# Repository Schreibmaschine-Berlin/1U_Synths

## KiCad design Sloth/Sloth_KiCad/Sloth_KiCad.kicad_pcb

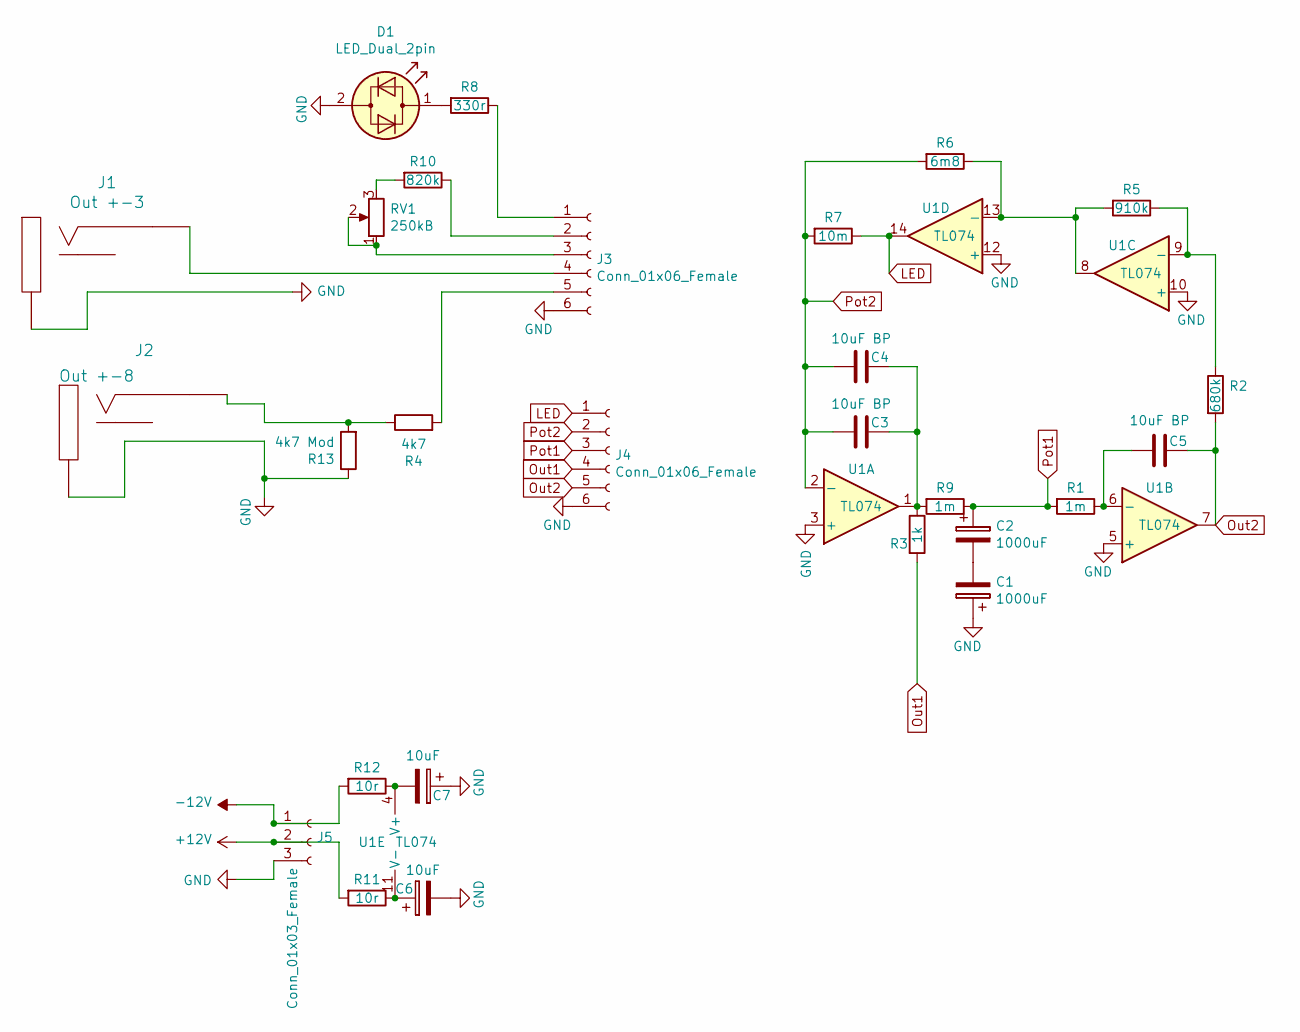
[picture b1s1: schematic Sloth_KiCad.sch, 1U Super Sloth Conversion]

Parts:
C1, C2: 1000uF; CP_Elec_10x10
C3, C4, C5: 10uF BP; CP_Elec_6.3x5.4_Nichicon
C6, C7: 10uF; CP_Elec_5x4.5
D1: LED_Dual_2pin; LED_D3.0mm
J1: Out +-3; PJ301M-12
J2: Out +-8; PJ301M-12
J3, J4: Conn_01x06_Female; PinHeader_1x06_P2.54mm_Vertical
J5: Conn_01x03_Female; PinHeader_1x03_P2.54mm_Vertical
R1, R9: 1m; R_0603_1608Metric_Pad1.05x0.95mm_HandSolder
R2: 680k; R_0603_1608Metric_Pad1.05x0.95mm_HandSolder
R3: 1k; R_0603_1608Metric_Pad1.05x0.95mm_HandSolder
R4: 4k7; R_0603_1608Metric_Pad1.05x0.95mm_HandSolder
R5: 910k; R_0603_1608Metric_Pad1.05x0.95mm_HandSolder
R6: 6m8; R_0603_1608Metric_Pad1.05x0.95mm_HandSolder
R7: 10m; R_0603_1608Metric_Pad1.05x0.95mm_HandSolder
R8: 330r; R_0603_1608Metric_Pad1.05x0.95mm_HandSolder
R10: 820k; R_0603_1608Metric_Pad1.05x0.95mm_HandSolder
R11, R12: 10r; R_0603_1608Metric_Pad1.05x0.95mm_HandSolder
R13: 4k7 Mod; R_0603_1608Metric_Pad1.05x0.95mm_HandSolder
RV1: 250kB; Potentiometer_Alps_RK09K_Single_Vertical
U1: TL074; SOIC-14_3.9x8.7mm_P1.27mm

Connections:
+12V: J5.2, R11.2
-12V: J5.1, R12.2
GND: C1.1, C6.2, C7.1, D1.2 (AK), J1.2 (SHEILD), J2.2 (SHEILD), J3.6, J4.6, J5.3, R13.1, U1.3 (+), U1.5 (+), U1.10 (+), U1.12 (+)
LED: J4.1, R7.1, U1.14
unnamed: C1.2, C2.2
unnamed: C3.1, C4.1, R3.1, R9.2, U1.1
unnamed: C5.2, R1.1, U1.6 (-)
unnamed: C6.1, R11.1, U1.11 (V-)
unnamed: C7.2, R12.1, U1.4 (V+)
unnamed: D1.1 (KA), R8.2
unnamed: J1.1 (SIG), J3.4
unnamed: J2.1 (SIG), R4.1, R13.2
unnamed: J3.1, R8.1
unnamed: J3.2, R10.1
unnamed: J3.3, RV1.1, RV1.2
unnamed: J3.5, R4.2
unnamed: R2.1, R5.1, U1.9 (-)
unnamed: R5.2, R6.1, U1.8, U1.13 (-)
unnamed: R10.2, RV1.3
Out1: J4.4, R3.2
Out2: C5.1, J4.5, R2.2, U1.7
Pot1: C2.1, J4.3, R1.2, R9.1
Pot2: C3.2, C4.2, J4.2, R6.2, R7.2, U1.2 (-)

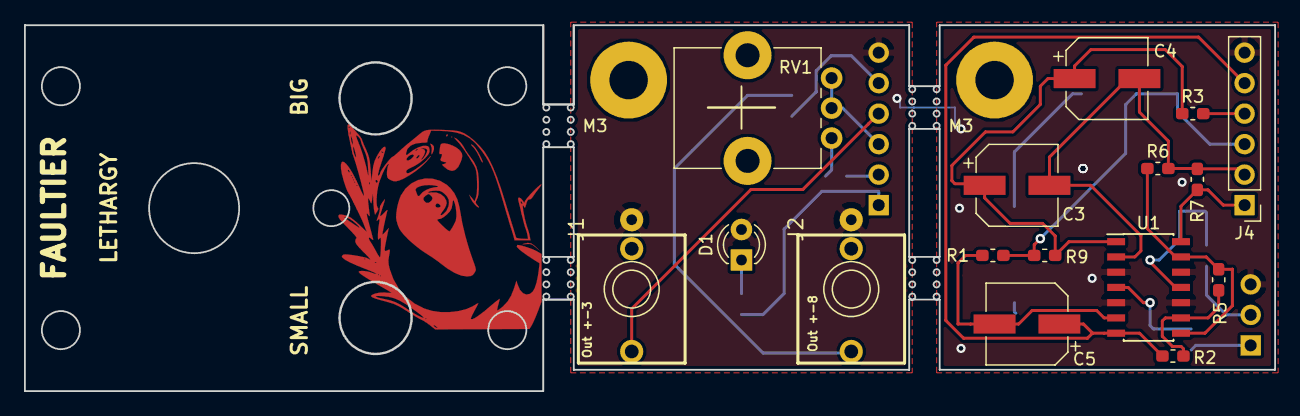
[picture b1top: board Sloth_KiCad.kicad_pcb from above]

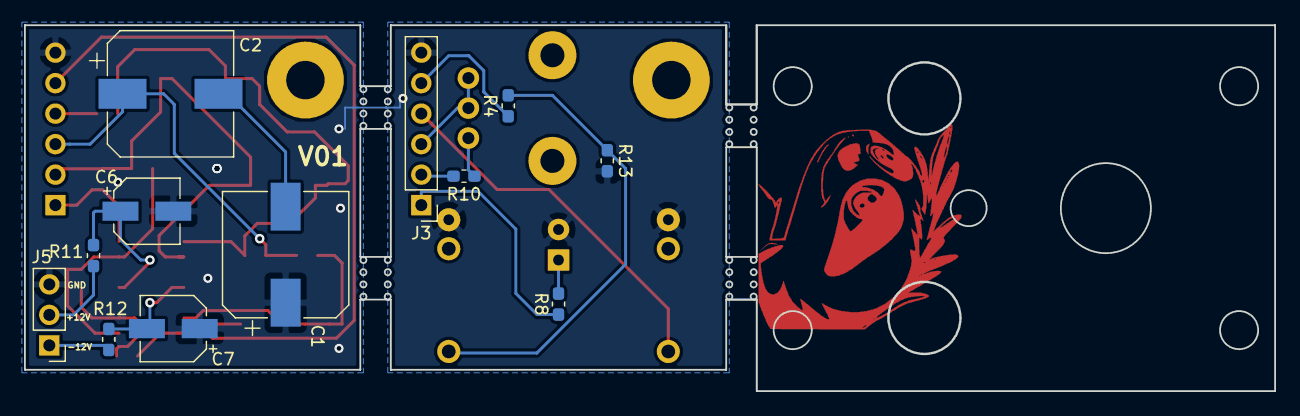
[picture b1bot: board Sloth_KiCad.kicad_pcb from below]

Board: 2 copper layers, 104.1 x 30.5 mm, 30 parts (12 on the bottom side), 23 nets.

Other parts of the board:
M3, M3#2: MountingHole_3.2mm_M3_Pad

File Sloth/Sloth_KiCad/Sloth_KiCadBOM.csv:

"Id";"Designator";"Package";"Quantity";"Designation";"Supplier and ref";
1;"M3,M3";"MountingHole_3.2mm_M3_Pad";2;"MountingHole_3.2mm_M3_Pad";;;
2;"C1,C2";"CP_Elec_10x10";2;"1000uF";;;
3;"C3,C4,C5";"CP_Elec_6.3x5.4_Nichicon";3;"10uF BP";;;
4;"C6,C7";"CP_Elec_5x4.5";2;"10uF";;;
5;"D1";"LED_D3.0mm";1;"LED_Dual_2pin";;;
6;"R1,R9";"R_0603_1608Metric_Pad1.05x0.95mm_HandSolder";2;"1m";;;
7;"R2";"R_0603_1608Metric_Pad1.05x0.95mm_HandSolder";1;"680k";;;
8;"R3";"R_0603_1608Metric_Pad1.05x0.95mm_HandSolder";1;"1k";;;
9;"R4";"R_0603_1608Metric_Pad1.05x0.95mm_HandSolder";1;"4k7";;;
10;"R5";"R_0603_1608Metric_Pad1.05x0.95mm_HandSolder";1;"910k";;;
11;"R6";"R_0603_1608Metric_Pad1.05x0.95mm_HandSolder";1;"6m8";;;
12;"R7";"R_0603_1608Metric_Pad1.05x0.95mm_HandSolder";1;"10m";;;
13;"R8";"R_0603_1608Metric_Pad1.05x0.95mm_HandSolder";1;"330r";;;
14;"R10";"R_0603_1608Metric_Pad1.05x0.95mm_HandSolder";1;"820k";;;
15;"R11,R12";"R_0603_1608Metric_Pad1.05x0.95mm_HandSolder";2;"10r";;;
16;"R13";"R_0603_1608Metric_Pad1.05x0.95mm_HandSolder";1;"4k7 Mod";;;
17;"RV1";"Potentiometer_Alps_RK09K_Single_Vertical";1;"250kB";;;
18;"U1";"SOIC-14_3.9x8.7mm_P1.27mm";1;"TL074";;;
19;"J4,J3";"PinHeader_1x06_P2.54mm_Vertical";2;"Conn_01x06_Female";;;
20;"J5";"PinHeader_1x03_P2.54mm_Vertical";1;"Conn_01x03_Female";;;
21;"J1";"PJ301M-12";1;"Out +-3";;;
22;"J2";"PJ301M-12";1;"Out +-8";;;
23;"G***";"Sloth2Mask";1;"LOGO";;;
24;"G***";"Sloth2Cu";1;"LOGO";;;

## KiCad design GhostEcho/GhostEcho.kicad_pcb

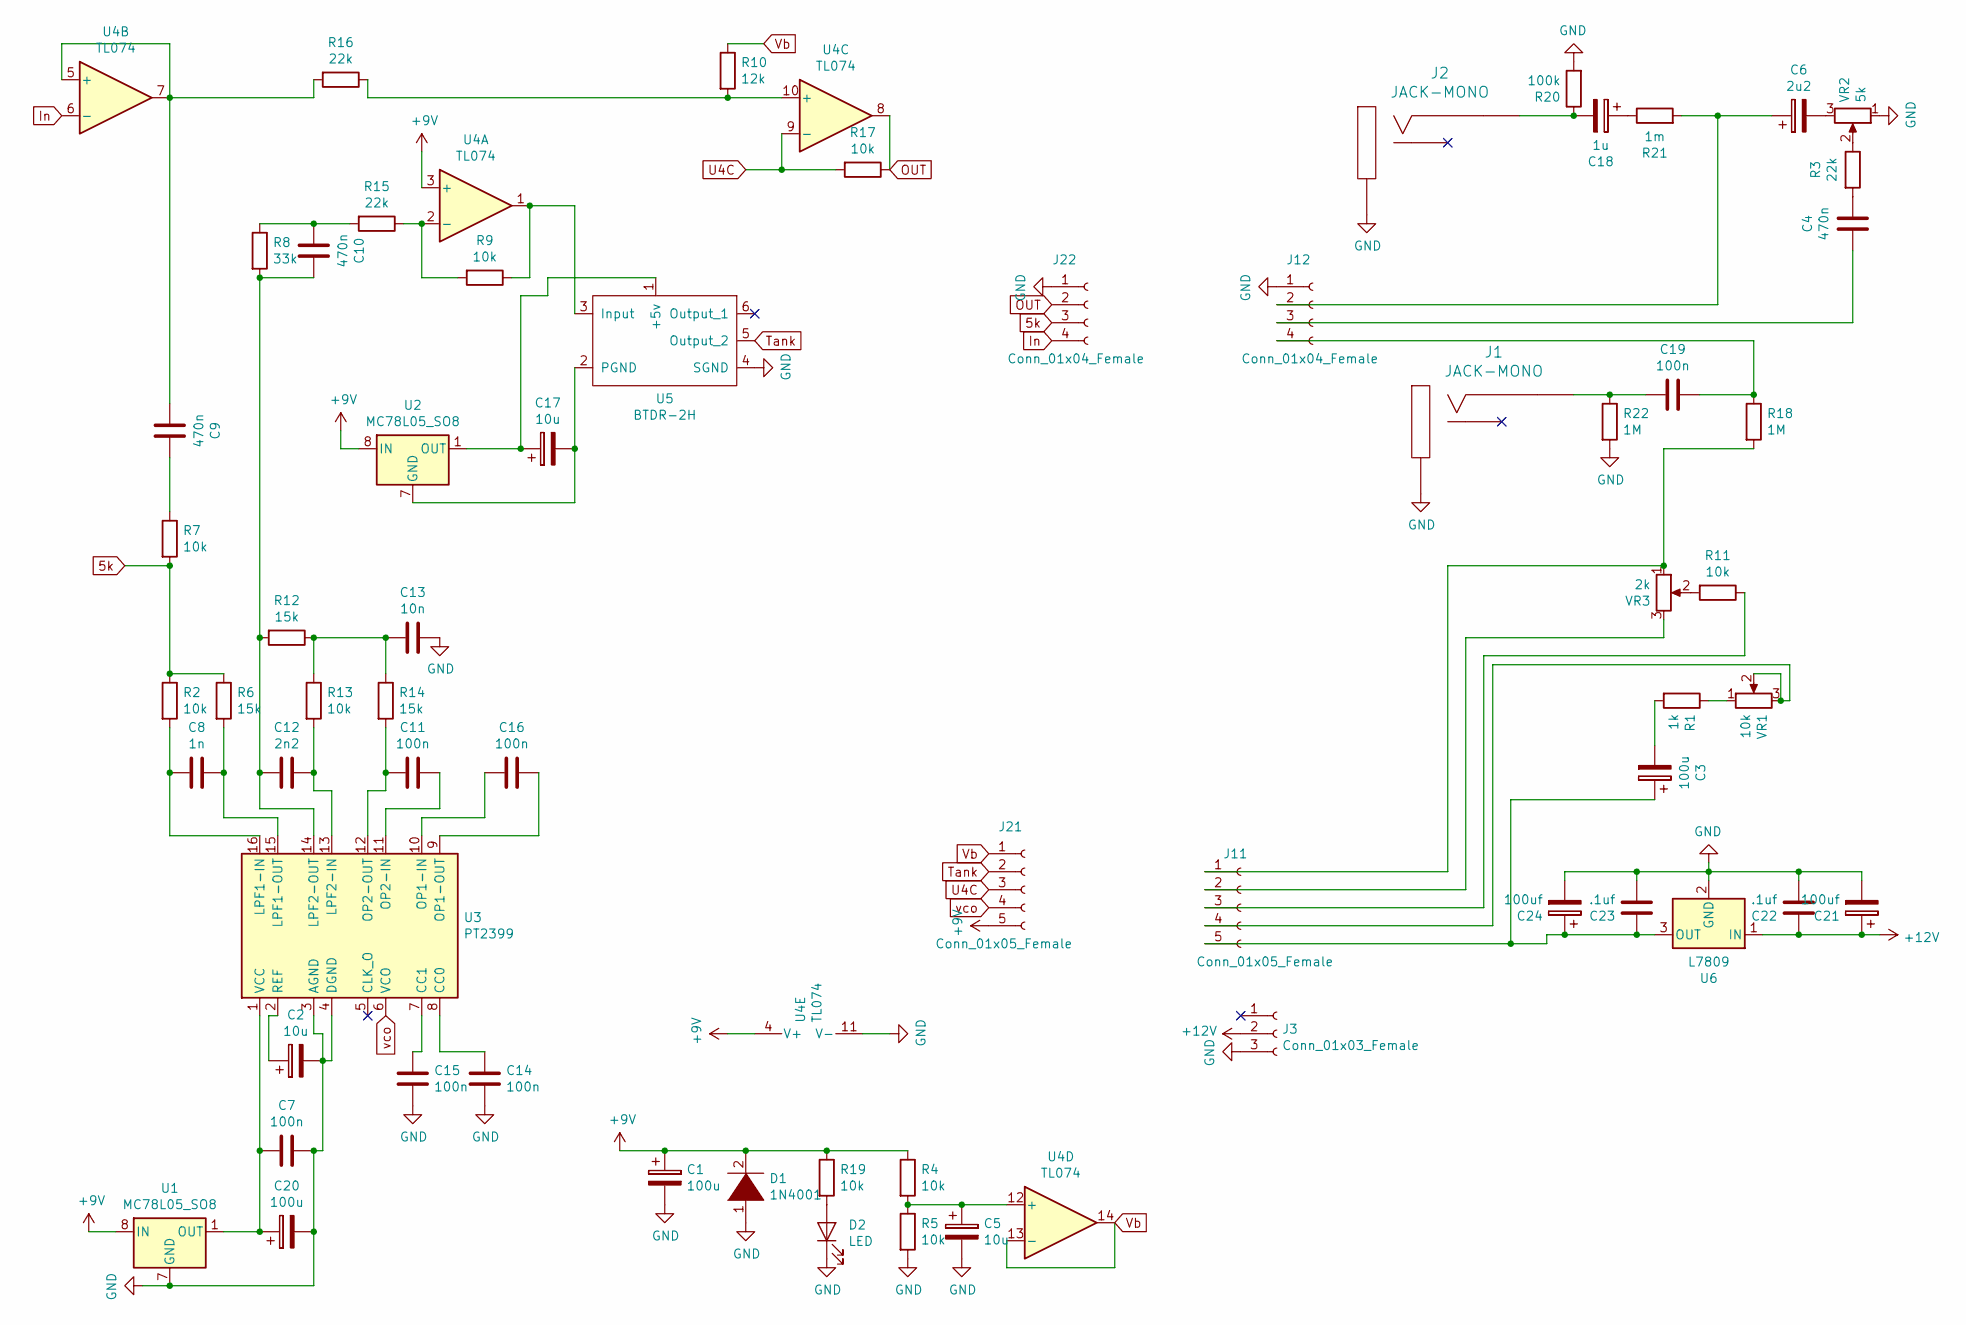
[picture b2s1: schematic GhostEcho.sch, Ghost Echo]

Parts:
C1, C3, C20: 100u; CP_Elec_6.3x7.7
C2, C5, C17: 10u; CP_Elec_6.3x7.7
C4, C9, C10: 470n; C_0603_1608Metric_Pad1.05x0.95mm_HandSolder
C6: 2u2; CP_Elec_6.3x7.7
C7, C11, C14, C15, C16, C19: 100n; C_0603_1608Metric_Pad1.05x0.95mm_HandSolder
C8: 1n; C_0603_1608Metric_Pad1.05x0.95mm_HandSolder
C12: 2n2; C_0603_1608Metric_Pad1.05x0.95mm_HandSolder
C13: 10n; C_0603_1608Metric_Pad1.05x0.95mm_HandSolder
C18: 1u; CP_Elec_6.3x7.7
C21, C24: 100uf; CP_Elec_6.3x7.7
C22, C23: .1uf; C_0603_1608Metric_Pad1.05x0.95mm_HandSolder
D1: 1N4001; D_MELF_Handsoldering
D2: LED; LED_D3.0mm
J1, J2: JACK-MONO; PJ301M-12
J3: Conn_01x03_Female; PinHeader_1x03_P2.54mm_Vertical
J11, J21: Conn_01x05_Female; PinSocket_1x05_P2.54mm_Vertical
J12, J22: Conn_01x04_Female; PinSocket_1x04_P2.54mm_Vertical
R1: 1k; R_0603_1608Metric_Pad1.05x0.95mm_HandSolder
R2, R4, R5, R7, R9, R11, R13, R17, R19: 10k; R_0603_1608Metric_Pad1.05x0.95mm_HandSolder
R3, R15, R16: 22k; R_0603_1608Metric_Pad1.05x0.95mm_HandSolder
R6, R12, R14: 15k; R_0603_1608Metric_Pad1.05x0.95mm_HandSolder
R8: 33k; R_0603_1608Metric_Pad1.05x0.95mm_HandSolder
R10: 12k; R_0603_1608Metric_Pad1.05x0.95mm_HandSolder
R18, R22: 1M; R_0603_1608Metric_Pad1.05x0.95mm_HandSolder
R20: 100k; R_0603_1608Metric_Pad1.05x0.95mm_HandSolder
R21: 1m; R_0603_1608Metric_Pad1.05x0.95mm_HandSolder
U1, U2: MC78L05_SO8; SOIC-8_3.9x4.9mm_P1.27mm
U3: PT2399; DIP-16_W8.89mm_SMDSocket_LongPads
U4: TL074; SOIC-14_3.9x8.7mm_P1.27mm
U5: BTDR-2H
U6: L7809; TO-252-3_TabPin2
VR1: 10k; BOURNS-PTA2043_20mm-slide-pot
VR2: 5k; BOURNS-PTA2043_20mm-slide-pot
VR3: 2k; BOURNS-PTA2043_20mm-slide-pot

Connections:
5k: J22.3, R2.1, R6.1, R7.2
+9V: C1.1, D1.2 (A), J21.5, R4.1, R19.1, U1.8 (IN), U2.8 (IN), U4.3 (+), U4.4 (V+)
+12V: C21.1, C22.1, J3.2, U6.1 (IN)
GND: C1.2, C2.2, C5.2, C7.2, C13.1, C14.2, C15.2, C20.2, C21.2, C22.2, C23.2, C24.2, D1.1 (K), D2.1 (K), J1.2 (SHEILD), J2.2 (SHEILD), J3.3, J12.1, J22.1, R5.2, R20.2, R22.2, U1.2 (GND), U1.3 (GND), U1.6 (GND), U1.7 (GND), U3.3 (AGND), U3.4 (DGND), U4.11 (V-), U5.4 (SGND), U6.2 (GND), VR2.1
In: J22.4, U4.6 (-)
unnamed: C2.1, U3.2 (REF)
unnamed: C3.2, R1.2
unnamed: C4.1, R3.2
unnamed: C4.2, J12.3
unnamed: C5.1, R4.2, R5.1, U4.12 (+)
unnamed: C6.1, J12.2, R21.2
unnamed: C6.2, VR2.3
unnamed: C8.1, R6.2, U3.15 (LPF1-OUT)
unnamed: C8.2, R2.2, U3.16 (LPF1-IN)
unnamed: C9.1, R7.1
unnamed: C9.2, R16.2, U4.5 (+), U4.7
unnamed: C10.1, C12.2, R8.2, R12.2, U3.14 (LPF2-OUT)
unnamed: C10.2, R8.1, R15.2
unnamed: C11.1, U3.11 (OP2-IN)
unnamed: C11.2, R14.2, U3.12 (OP2-OUT)
unnamed: C12.1, R13.2, U3.13 (LPF2-IN)
unnamed: C13.2, R12.1, R13.1, R14.1
unnamed: C14.1, U3.8 (CC0)
unnamed: C15.1, U3.7 (CC1)
unnamed: C16.1, U3.9 (OP1-OUT)
unnamed: C16.2, U3.10 (OP1-IN)
unnamed: C17.1, U2.1 (OUT), U5.1 (+5v)
unnamed: C17.2, U2.2 (GND), U2.3 (GND), U2.6 (GND), U2.7 (GND), U5.2 (PGND)
unnamed: C18.1, R21.1
unnamed: C18.2, J2.1 (SIG), R20.1
unnamed: C19.1, J12.4, R18.1
unnamed: C19.2, J1.1 (SIG), R22.1
unnamed: C7.1, C20.1, U1.1 (OUT), U3.1 (VCC)
unnamed: C3.1, C23.1, C24.1, J11.5, U6.3 (OUT)
unnamed: D2.2 (A), R19.2
unnamed: J11.1, R18.2, VR3.1
unnamed: J11.2, VR3.3
unnamed: J11.3, R11.1
unnamed: J11.4, VR1.2, VR1.3
unnamed: R1.1, VR1.1
unnamed: R3.1, VR2.2
unnamed: R9.1, U4.1, U5.3 (Input)
unnamed: R10.2, R16.1, U4.10 (+)
unnamed: R11.2, VR3.2
unnamed: R9.2, R15.1, U4.2 (-)
OUT: J22.2, R17.1, U4.8
Tank: J21.2, U5.5 (Output_2)
U4C: J21.3, R17.2, U4.9 (-)
Vb: J21.1, R10.1, U4.13 (-), U4.14
vco: J21.4, U3.6 (VCO)

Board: 2 copper layers, 64 parts (52 on the bottom side), 50 nets, no tracks yet.

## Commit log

2019-01-03 Added Sloth Clone and Blind Panels
2019-01-03 Added Benjolin Conversion Project
2019-01-04 Nearly done with schematic
2019-01-05 Added footprints
2019-01-22 Added Ghost Echo
2019-07-10 Update to Sloth
